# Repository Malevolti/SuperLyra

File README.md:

A custom mechanical ergo keyboard by Dom.

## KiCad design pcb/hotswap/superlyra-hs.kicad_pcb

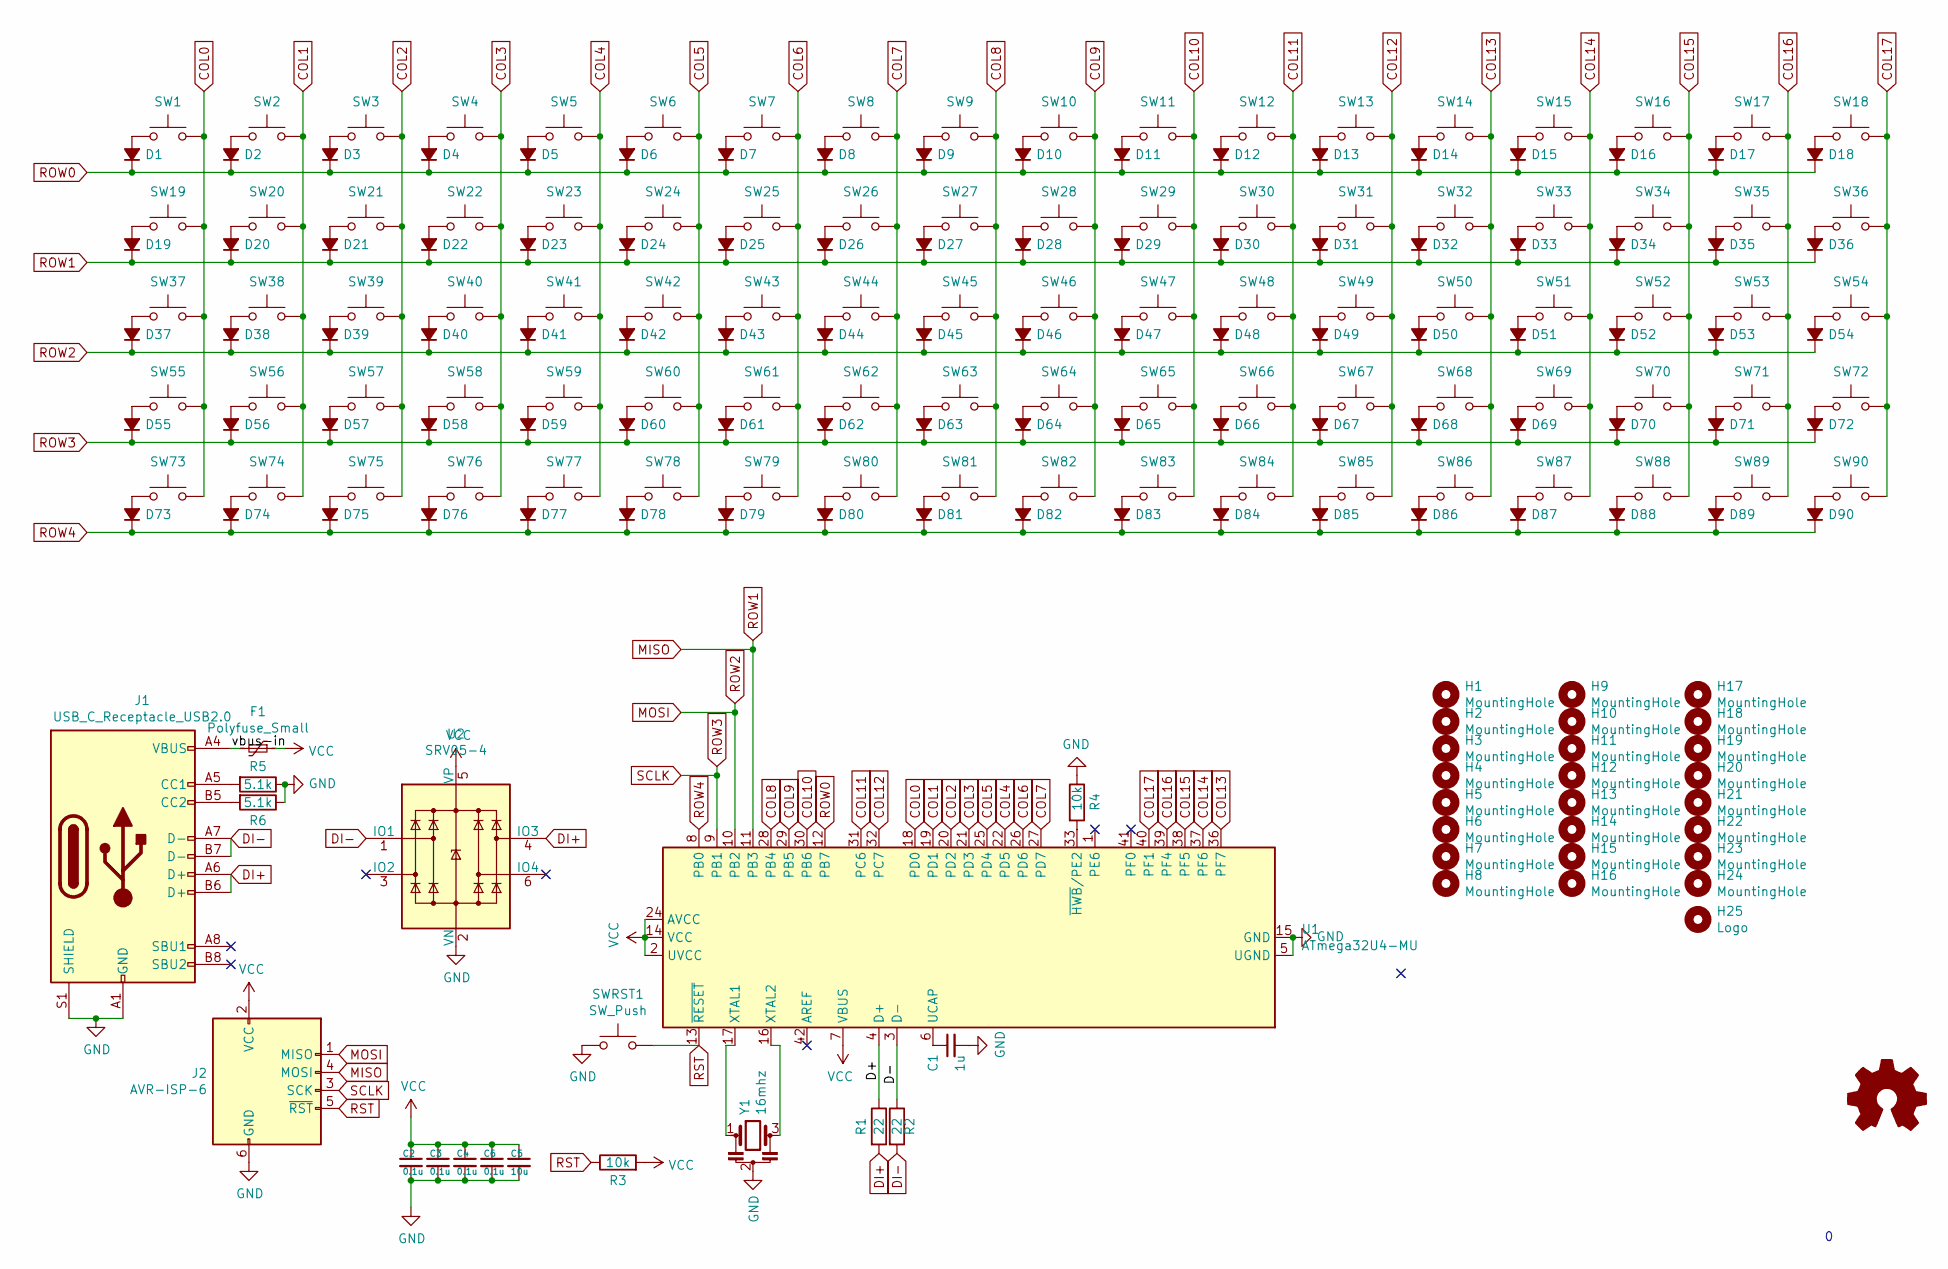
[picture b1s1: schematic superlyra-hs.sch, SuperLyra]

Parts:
C1: 1u; C_0402; LCSC C106253
C2, C3, C4, C6: 0.1u; C_0402; LCSC C106204
C5: 10u; C_0402; LCSC C237279
D1, D2, D3, D4, D5, D6, D7, D8, D9, D10, D11, D12, D13, D14, D15, D16, D17, D18, D19, D20, D21, D22, D23, D24, D25, D26, D27, D28, D29, D30, D31, D32, D33, D34, D35, D36, D37, D38, D39, D40, D41, D42, D43, D44, D45, D46, D47, D48, D49, D50, D51, D52, D53, D54, D55, D56, D57, D58, D59, D60, D61, D62, D63, D64, D65, D66, D67, D68, D69, D70, D71, D72, D73, D74, D75, D76, D77, D78, D79, D80, D81, D82, D83, D84, D85, D86, D87, D88, D89, D90: D_Small_ALT; D_SOD-123F; LCSC C2099
F1: Polyfuse_Small; Fuse_0402_1005Metric; LCSC C914085
H1, H2, H3, H4, H5, H6, H7, H8, H9, H10, H11, H12, H13, H14, H15, H16, H17, H18, H19, H20, H21, H22, H23, H24: MountingHole; MountingHole_2.2mm_M2_ISO7380_Pad
H25: Logo; SuperLyraLogo
J1: USB_C_Receptacle_USB2.0; USB_C_Receptacle_HRO_TYPE-C-31-M-12; LCSC C165948
J2: AVR-ISP-6; PinSocket_2x03_P2.54mm_Vertical
R1, R2: 22; R_0402_1005Metric_Pad0.72x0.64mm_HandSolder; LCSC C93929
R3, R4: 10k; R_0402_1005Metric_Pad0.72x0.64mm_HandSolder; LCSC C60489
R5, R6: 5.1k; R_0402_1005Metric_Pad0.72x0.64mm_HandSolder; LCSC C25905
SW1, SW2, SW3, SW4, SW5, SW6, SW7, SW8, SW9, SW10, SW11, SW12, SW13, SW14, SW15, SW16, SW17, SW18, SW19, SW20, SW21, SW22, SW23, SW24, SW25, SW26, SW27, SW28, SW29, SW30, SW31, SW32, SW33, SW34, SW35, SW36, SW37, SW38, SW39, SW40, SW41, SW42, SW43, SW44, SW45, SW46, SW47, SW48, SW49, SW50, SW51, SW52, SW53, SW54, SW55, SW56, SW57, SW58, SW59, SW60, SW61, SW62, SW63, SW64, SW65, SW66, SW67, SW68, SW69, SW70, SW71, SW72, SW73, SW74, SW75, SW76, SW77, SW78, SW80, SW81, SW82, SW83, SW85, SW86, SW87, SW88, SW89, SW90: SW_Push; MX_Socket_18mmSingleSided
SW79, SW84: SW_Push; MX-2U-StabFlip
SWRST1: SW_Push; SW_SPST_TL3342; LCSC C318884
U1: ATmega32U4-MU; QFN-44-1EP_7x7mm_P0.5mm_EP5.2x5.2mm; LCSC C112161
U2: SRV05-4; SOT-23-6; LCSC C558418
Y1: 16mhz; Resonator_SMD_muRata_CSTxExxV-3Pin_3.0x1.1mm; LCSC C341521

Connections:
/D+: R1.1, U1.4 (D+)
/D-: R2.1, U1.3 (D-)
/vbus-in: F1.2, J1.A4 (VBUS), J1.A9 (VBUS), J1.B4 (VBUS), J1.B9 (VBUS)
COL0: SW1.2, SW19.2, SW37.2, SW55.2, SW73.2, U1.18 (PD0)
COL1: SW2.2, SW20.2, SW38.2, SW56.2, SW74.2, U1.19 (PD1)
COL2: SW3.2, SW21.2, SW39.2, SW57.2, SW75.2, U1.20 (PD2)
COL3: SW4.2, SW22.2, SW40.2, SW58.2, SW76.2, U1.21 (PD3)
COL4: SW5.2, SW23.2, SW41.2, SW59.2, SW77.2, U1.22 (PD5)
COL5: SW6.2, SW24.2, SW42.2, SW60.2, SW78.2, U1.25 (PD4)
COL6: SW7.2, SW25.2, SW43.2, SW61.2, SW79.2, U1.26 (PD6)
COL7: SW8.2, SW26.2, SW44.2, SW62.2, SW80.2, U1.27 (PD7)
COL8: SW9.2, SW27.2, SW45.2, SW63.2, SW81.2, U1.28 (PB4)
COL9: SW10.2, SW28.2, SW46.2, SW64.2, SW82.2, U1.29 (PB5)
COL10: SW11.2, SW29.2, SW47.2, SW65.2, SW83.2, U1.30 (PB6)
COL11: SW12.2, SW30.2, SW48.2, SW66.2, SW84.2, U1.31 (PC6)
COL12: SW13.2, SW31.2, SW49.2, SW67.2, SW85.2, U1.32 (PC7)
COL13: SW14.2, SW32.2, SW50.2, SW68.2, SW86.2, U1.36 (PF7)
COL14: SW15.2, SW33.2, SW51.2, SW69.2, SW87.2, U1.37 (PF6)
COL15: SW16.2, SW34.2, SW52.2, SW70.2, SW88.2, U1.38 (PF5)
COL16: SW17.2, SW35.2, SW53.2, SW71.2, SW89.2, U1.39 (PF4)
COL17: SW18.2, SW36.2, SW54.2, SW72.2, SW90.2, U1.40 (PF1)
DI+: J1.A6 (D+), J1.B6 (D+), R1.2, U2.4 (IO3)
DI-: J1.A7 (D-), J1.B7 (D-), R2.2, U2.1 (IO1)
GND: C1.2, C2.2, C3.2, C4.2, C5.2, C6.2, J1.A1 (GND), J1.A12 (GND), J1.B1 (GND), J1.B12 (GND), J1.S1 (SHIELD), J2.6 (GND), R4.1, R5.1, R6.1, SWRST1.1, U1.5 (UGND), U1.15 (GND), U1.23 (GND), U1.35 (GND), U1.43 (GND), U1.45 (GND), U2.2 (VN), Y1.2
MISO: D19.1 (K), D20.1 (K), D21.1 (K), D22.1 (K), D23.1 (K), D24.1 (K), D25.1 (K), D26.1 (K), D27.1 (K), D28.1 (K), D29.1 (K), D30.1 (K), D31.1 (K), D32.1 (K), D33.1 (K), D34.1 (K), D35.1 (K), D36.1 (K), J2.4 (MOSI), U1.11 (PB3)
MOSI: D37.1 (K), D38.1 (K), D39.1 (K), D40.1 (K), D41.1 (K), D42.1 (K), D43.1 (K), D44.1 (K), D45.1 (K), D46.1 (K), D47.1 (K), D48.1 (K), D49.1 (K), D50.1 (K), D51.1 (K), D52.1 (K), D53.1 (K), D54.1 (K), J2.1 (MISO), U1.10 (PB2)
unnamed: C1.1, U1.6 (UCAP)
unnamed: D1.2 (A), SW1.1
unnamed: D2.2 (A), SW2.1
unnamed: D3.2 (A), SW3.1
unnamed: D4.2 (A), SW4.1
unnamed: D5.2 (A), SW5.1
unnamed: D6.2 (A), SW6.1
unnamed: D7.2 (A), SW7.1
unnamed: D8.2 (A), SW8.1
unnamed: D9.2 (A), SW9.1
unnamed: D10.2 (A), SW10.1
unnamed: D11.2 (A), SW11.1
unnamed: D12.2 (A), SW12.1
unnamed: D13.2 (A), SW13.1
unnamed: D14.2 (A), SW14.1
unnamed: D15.2 (A), SW15.1
unnamed: D16.2 (A), SW16.1
unnamed: D17.2 (A), SW17.1
unnamed: D18.2 (A), SW18.1
unnamed: D19.2 (A), SW19.1
unnamed: D20.2 (A), SW20.1
unnamed: D21.2 (A), SW21.1
unnamed: D22.2 (A), SW22.1
unnamed: D23.2 (A), SW23.1
unnamed: D24.2 (A), SW24.1
unnamed: D25.2 (A), SW25.1
unnamed: D26.2 (A), SW26.1
unnamed: D27.2 (A), SW27.1
unnamed: D28.2 (A), SW28.1
unnamed: D29.2 (A), SW29.1
unnamed: D30.2 (A), SW30.1
unnamed: D31.2 (A), SW31.1
unnamed: D32.2 (A), SW32.1
unnamed: D33.2 (A), SW33.1
unnamed: D34.2 (A), SW34.1
unnamed: D35.2 (A), SW35.1
unnamed: D36.2 (A), SW36.1
unnamed: D37.2 (A), SW37.1
unnamed: D38.2 (A), SW38.1
unnamed: D39.2 (A), SW39.1
unnamed: D40.2 (A), SW40.1
unnamed: D41.2 (A), SW41.1
unnamed: D42.2 (A), SW42.1
unnamed: D43.2 (A), SW43.1
unnamed: D44.2 (A), SW44.1
unnamed: D45.2 (A), SW45.1
unnamed: D46.2 (A), SW46.1
unnamed: D47.2 (A), SW47.1
unnamed: D48.2 (A), SW48.1
unnamed: D49.2 (A), SW49.1
unnamed: D50.2 (A), SW50.1
unnamed: D51.2 (A), SW51.1
unnamed: D52.2 (A), SW52.1
unnamed: D53.2 (A), SW53.1
unnamed: D54.2 (A), SW54.1
unnamed: D55.2 (A), SW55.1
unnamed: D56.2 (A), SW56.1
unnamed: D57.2 (A), SW57.1
unnamed: D58.2 (A), SW58.1
unnamed: D59.2 (A), SW59.1
unnamed: D60.2 (A), SW60.1
unnamed: D61.2 (A), SW61.1
unnamed: D62.2 (A), SW62.1
unnamed: D63.2 (A), SW63.1
unnamed: D64.2 (A), SW64.1
unnamed: D65.2 (A), SW65.1
unnamed: D66.2 (A), SW66.1
unnamed: D67.2 (A), SW67.1
unnamed: D68.2 (A), SW68.1
unnamed: D69.2 (A), SW69.1
unnamed: D70.2 (A), SW70.1
unnamed: D71.2 (A), SW71.1
unnamed: D72.2 (A), SW72.1
unnamed: D73.2 (A), SW73.1
unnamed: D74.2 (A), SW74.1
unnamed: D75.2 (A), SW75.1
unnamed: D76.2 (A), SW76.1
unnamed: D77.2 (A), SW77.1
unnamed: D78.2 (A), SW78.1
unnamed: D79.2 (A), SW79.1
unnamed: D80.2 (A), SW80.1
unnamed: D81.2 (A), SW81.1
unnamed: D82.2 (A), SW82.1
unnamed: D83.2 (A), SW83.1
unnamed: D84.2 (A), SW84.1
unnamed: D85.2 (A), SW85.1
unnamed: D86.2 (A), SW86.1
unnamed: D87.2 (A), SW87.1
unnamed: D88.2 (A), SW88.1
unnamed: D89.2 (A), SW89.1
unnamed: D90.2 (A), SW90.1
unnamed: J1.A5 (CC1), R5.2
unnamed: J1.B5 (CC2), R6.2
unnamed: R4.2, U1.33 (~HWB~/PE2)
unnamed: U1.16 (XTAL2), Y1.3
unnamed: U1.17 (XTAL1), Y1.1
ROW0: D1.1 (K), D2.1 (K), D3.1 (K), D4.1 (K), D5.1 (K), D6.1 (K), D7.1 (K), D8.1 (K), D9.1 (K), D10.1 (K), D11.1 (K), D12.1 (K), D13.1 (K), D14.1 (K), D15.1 (K), D16.1 (K), D17.1 (K), D18.1 (K), U1.12 (PB7)
ROW3: D55.1 (K), D56.1 (K), D57.1 (K), D58.1 (K), D59.1 (K), D60.1 (K), D61.1 (K), D62.1 (K), D63.1 (K), D64.1 (K), D65.1 (K), D66.1 (K), D67.1 (K), D68.1 (K), D69.1 (K), D70.1 (K), D71.1 (K), D72.1 (K), J2.3 (SCK), U1.9 (PB1)
ROW4: D73.1 (K), D74.1 (K), D75.1 (K), D76.1 (K), D77.1 (K), D78.1 (K), D79.1 (K), D80.1 (K), D81.1 (K), D82.1 (K), D83.1 (K), D84.1 (K), D85.1 (K), D86.1 (K), D87.1 (K), D88.1 (K), D89.1 (K), D90.1 (K), U1.8 (PB0)
RST: J2.5 (~RST), R3.1, SWRST1.2, U1.13 (~RESET)
VCC: C2.1, C3.1, C4.1, C5.1, C6.1, F1.1, J2.2 (VCC), R3.2, U1.2 (UVCC), U1.7 (VBUS), U1.14 (VCC), U1.24 (AVCC), U1.34 (VCC), U1.44 (AVCC), U2.5 (VP)

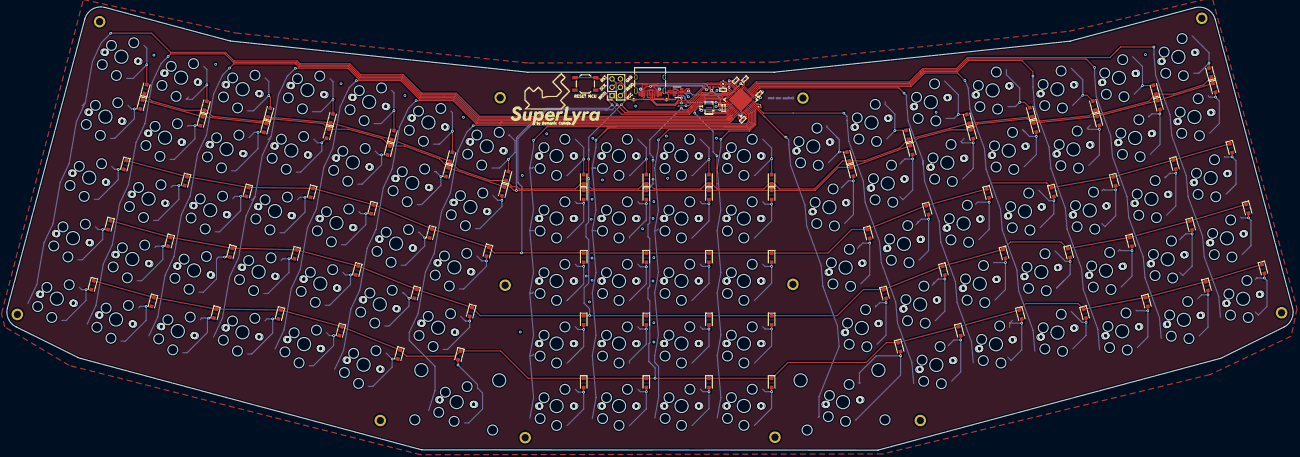
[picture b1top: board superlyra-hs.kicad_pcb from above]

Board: 2 copper layers, 391.1 x 134.8 mm, 212 parts (0 on the bottom side), 127 nets.

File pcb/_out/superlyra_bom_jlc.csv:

"Comment","Designator","Footprint","LCSC Part #"
"1u","C1","C_0402","C106253"
"0.1u","C2,C4,C3,C6","C_0402","C106204"
"10u","C5","C_0402","C237279"
"D_Small_ALT","D90,D89,D88,D87,D86,D85,D84,D83,D82,D81,D80,D79,D78,D77,D76,D75,D74,D73,D72,D71,D70,D69,D68,D67,D66,D65,D64,D63,D62,D61,D60,D59,D58,D57,D56,D55,D54,D53,D52,D51,D50,D49,D48,D47,D46,D45,D44,D43,D42,D41,D40,D39,D38,D37,D36,D35,D34,D33,D32,D31,D30,D29,D28,D27,D26,D25,D24,D23,D22,D21,D20,D19,D18,D17,D16,D15,D14,D13,D12,D11,D10,D9,D8,D7,D6,D1,D2,D3,D4,D5","D_SOD-123F","C2099"
"Polyfuse_Small","F1","Fuse_0402_1005Metric","C914085"
"MountingHole","H7,H1,H6,H5,H4,H3,H2,H8,H15,H9,H14,H13,H12,H11,H10,H16,H23,H17,H22,H21,H20,H19,H18,H24","MountingHole_2.2mm_M2_ISO7380_Pad","no_part_number"
"Logo","H25","SuperLyraLogo","no_part_number"
"USB_C_Receptacle_USB2.0","J1","USB_C_Receptacle_HRO_TYPE-C-31-M-12","C165948"
"AVR-ISP-6","J2","PinSocket_2x03_P2.54mm_Vertical","no_part_number"
"22","R2,R1","R_0402_1005Metric_Pad0.72x0.64mm_HandSolder","C93929"
"10k","R4,R3","R_0402_1005Metric_Pad0.72x0.64mm_HandSolder","C60489"
"5.1k","R6,R5","R_0402_1005Metric_Pad0.72x0.64mm_HandSolder","C25905"
"SW_Push","SW1,SW2,SW90,SW89,SW88,SW87,SW86,SW85,SW83,SW82,SW81,SW80,SW78,SW77,SW76,SW75,SW74,SW73,SW72,SW71,SW70,SW69,SW68,SW67,SW66,SW65,SW64,SW63,SW62,SW61,SW60,SW59,SW58,SW57,SW56,SW55,SW54,SW53,SW52,SW51,SW50,SW49,SW48,SW47,SW46,SW45,SW44,SW43,SW42,SW41,SW40,SW39,SW38,SW37,SW36,SW35,SW34,SW33,SW32,SW31,SW30,SW29,SW28,SW27,SW26,SW25,SW24,SW23,SW22,SW21,SW20,SW19,SW18,SW17,SW16,SW15,SW14,SW13,SW12,SW11,SW10,SW9,SW8,SW7,SW6,SW5,SW4,SW3","MX-Alps-Choc-1U-NoLED","no_part_number"
"SW_Push","SW84,SW79","MX-Alps-Choc-2U-StabFlip-NoLED","no_part_number"
"SW_Push","SWRST1","SW_SPST_TL3342","C318884"
"ATmega32U4-MU","U1","QFN-44-1EP_7x7mm_P0.5mm_EP5.2x5.2mm","C112161"
"SRV05-4","U2","SOT-23-6","C558418"
"16mhz","Y1","Resonator_SMD_muRata_CSTxExxV-3Pin_3.0x1.1mm_HandSoldering","C341521"

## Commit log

2021-09-12 initial
2021-09-12 update resonator
2021-09-13 move diodes to front side
2021-09-13 front ground fill update
2021-09-15 0.5 (evaluation)
2021-09-15 fixed missing connectons on some of the columns
2021-09-15 removed silkscreen for all the mount holes
2021-09-15 tidyup
2021-09-15 lots, see list
    - Added a power plane under the MCU
    - moved the CC resistors incase hand soldering is required
    - moved a via that was overlapping a different net trace
    - sorted DRC some DRC errors, mainly courtyard overlaps
    - added smol Easter egg
    - made some traces around the MCU slightly prettier.
2021-09-15 added lables for the reset button and ISP header. moved all references to cmts instead of silkscreen as it looks neater.,
2021-09-15 added readme for screenshot
2021-09-15 moved readme and screen to the right place
2021-09-15 removed background of PNG for embedding
2021-09-15 Envious Edits
2021-09-15 Moved all the traces I could find away from holes and edges to account for mechanical damage.
2021-09-15 added bat for jlc-kicad-tools to generate BOM and CPL later.
2021-09-16 update gnd fill
2021-09-16 Generated up-to-date gerbers for JLCPCB
2021-09-16 stuff
2021-10-09 add hotswap ver
